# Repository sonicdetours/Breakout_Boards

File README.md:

Breakout Boards
---------------

A couple of handy breakout boards boards for prototyping stuff. Oliver Gillet's "breadboard friends" were used as a starting point for the PCB layouts.

Note that dimensions vary slightly between breadboards from different manufacturers. Be sure to check that the PCB layouts match your board before you start etching!

Released under Creative Commons cc-by-sa 3.0 license.

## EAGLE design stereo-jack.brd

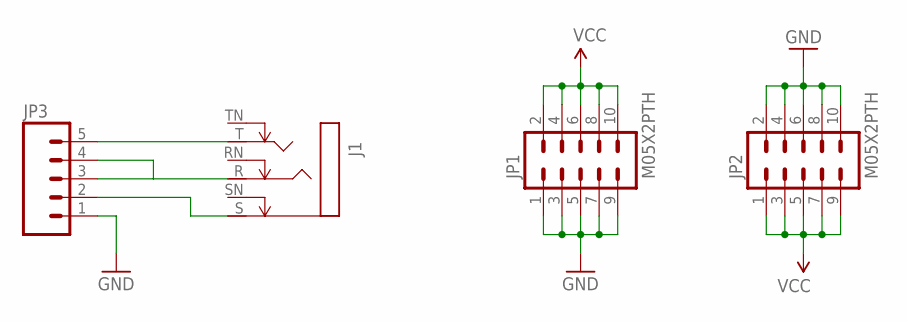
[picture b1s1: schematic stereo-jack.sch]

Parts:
J1: STEREOSW; NMJ6HCD2
JP1, JP2: M05X2PTH; AVR_ICSP
JP3: M05PTH; 1X05

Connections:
GND: JP1.1, JP1.3, JP1.5, JP1.7, JP1.9, JP2.2, JP2.4, JP2.6, JP2.8, JP2.10, JP3.1
unnamed: J1.S, JP3.2
unnamed: J1.R, JP3.3, JP3.4
unnamed: J1.T, JP3.5
VCC: JP1.2, JP1.4, JP1.6, JP1.8, JP1.10, JP2.1, JP2.3, JP2.5, JP2.7, JP2.9

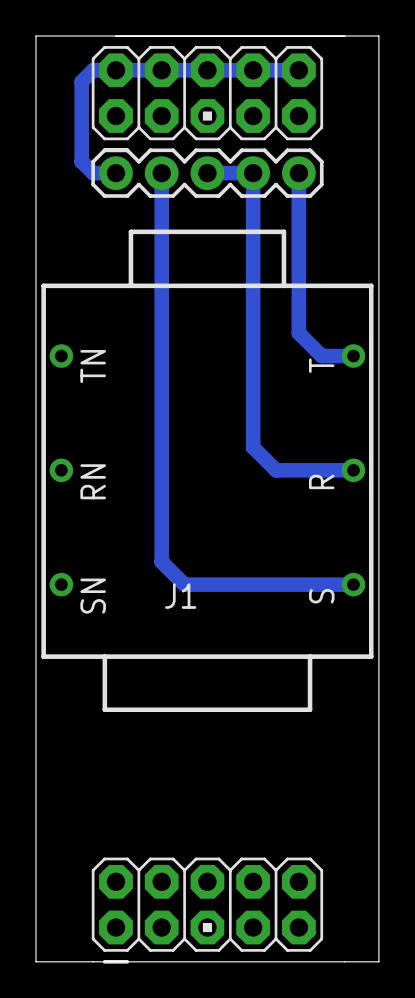
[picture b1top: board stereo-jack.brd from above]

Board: 2 copper layers, 19.0 x 51.4 mm, 4 parts (0 on the bottom side), 5 nets.

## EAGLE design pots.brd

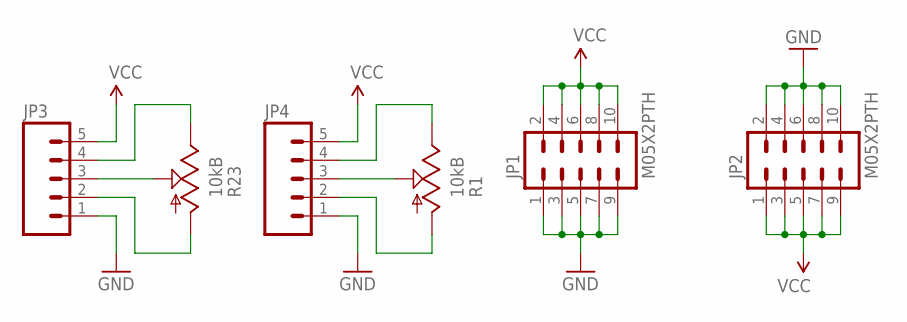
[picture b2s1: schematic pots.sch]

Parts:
JP1, JP2: M05X2PTH; AVR_ICSP
JP3, JP4: M05PTH; 1X05
R1, R23: 10kB; ALPS_POT_VERTICAL

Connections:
GND: JP1.1, JP1.3, JP1.5, JP1.7, JP1.9, JP2.2, JP2.4, JP2.6, JP2.8, JP2.10, JP3.1, JP4.1
unnamed: JP3.4, R23.P$1 (E)
unnamed: JP3.3, R23.P$2 (S)
unnamed: JP3.2, R23.P$3 (A)
unnamed: JP4.4, R1.P$1 (E)
unnamed: JP4.3, R1.P$2 (S)
unnamed: JP4.2, R1.P$3 (A)
VCC: JP1.2, JP1.4, JP1.6, JP1.8, JP1.10, JP2.1, JP2.3, JP2.5, JP2.7, JP2.9, JP3.5, JP4.5

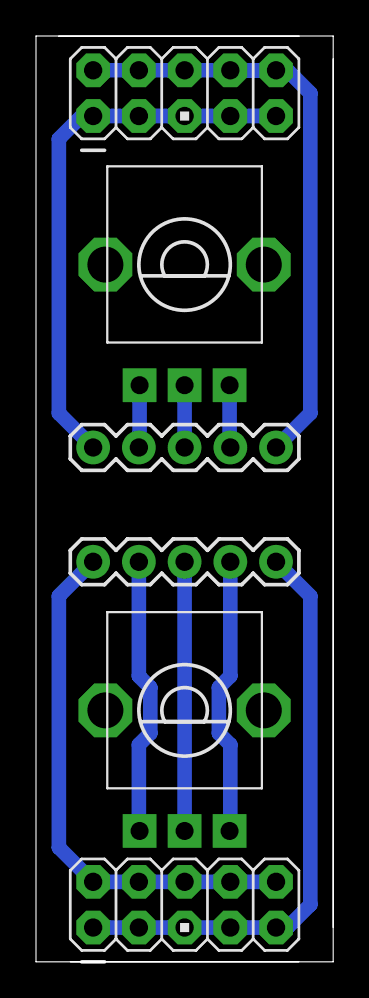
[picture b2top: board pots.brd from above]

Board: 2 copper layers, 16.5 x 51.4 mm, 6 parts (0 on the bottom side), 8 nets.

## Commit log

2014-08-03 Minor corrections
